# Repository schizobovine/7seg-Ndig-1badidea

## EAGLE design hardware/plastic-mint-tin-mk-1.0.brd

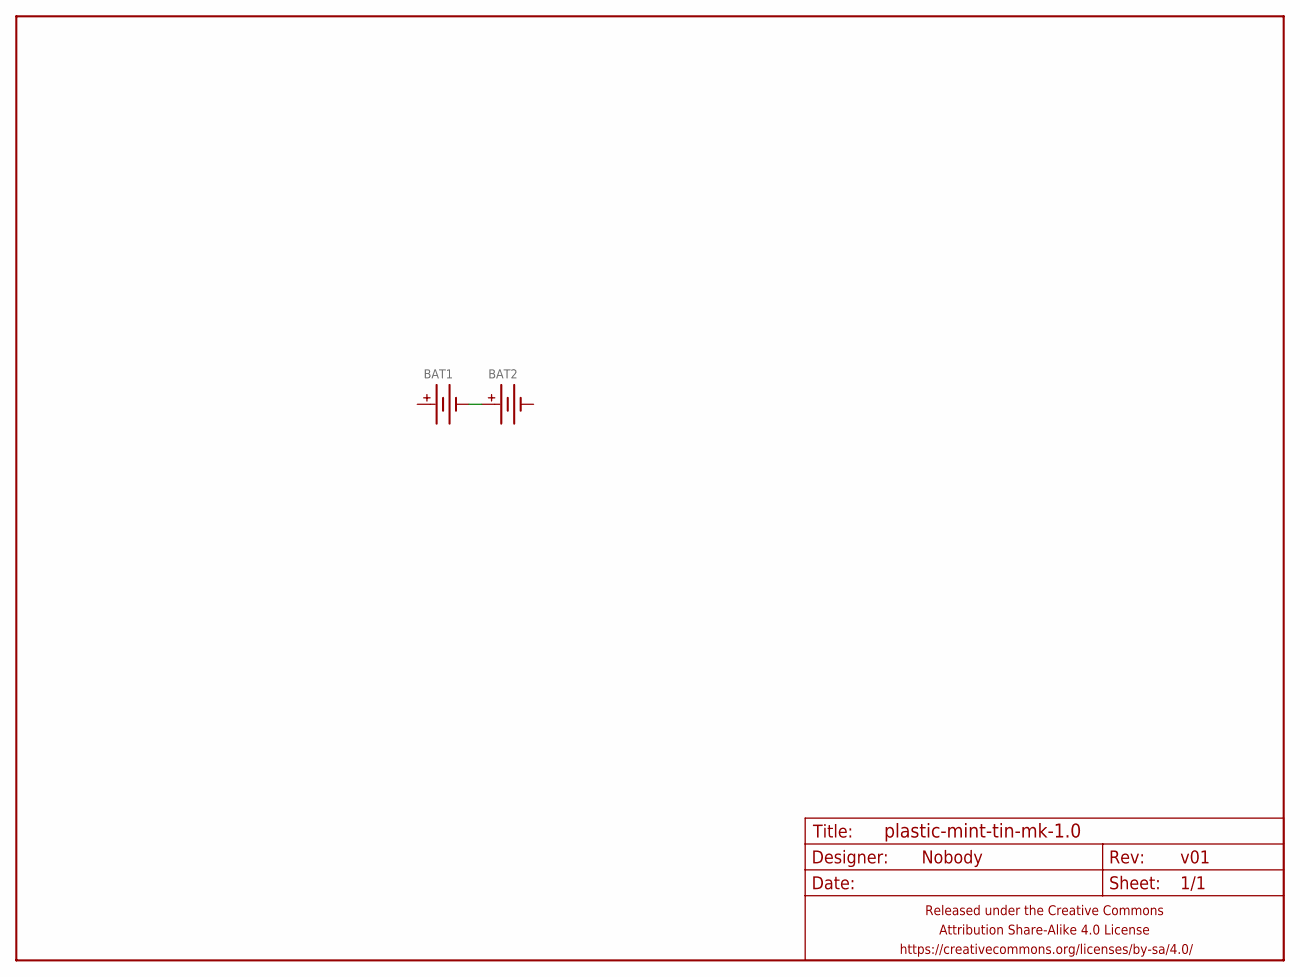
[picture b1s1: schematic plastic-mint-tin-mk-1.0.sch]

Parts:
BAT1, BAT2: BATTERYAA; BATTERY-AA
FRAME1: FRAME-LETTERNO_PACKAGE; DUMMY

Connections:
+: BAT1.PWR@1 (+), BAT1.PWR@2 (+)
-: BAT2.GND@1 (-), BAT2.GND@2 (-)
unnamed: BAT1.GND@1 (-), BAT1.GND@2 (-), BAT2.PWR@1 (+), BAT2.PWR@2 (+)

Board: 2 copper layers, 3 parts (0 on the bottom side), 3 nets, no tracks yet.

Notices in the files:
parts and their libraries:
A_butts: Released under the Creative Commons Attribution Share-Alike 4.0 License
A_butts: https://creativecommons.org/licenses/by-sa/4.0
A_butts: Released under the Creative Commons
